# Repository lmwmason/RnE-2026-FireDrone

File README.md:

# FireDrone

FireDrone is an R&E research project on fault-aware flight-control firmware for a robotic-arm-equipped firefighting drone. It combines two distinct development tracks:

- **Mobula8 research firmware**: a real STM32F405 quadrotor running a patched Betaflight 4.4.2 build, used to validate embedded attitude estimation, bounded rate correction, logging, and safety fallbacks.
- **FireDrone X8 simulator**: a real-time X8/coaxial simulation for design studies involving wind, actuator and sensor faults, and robotic-arm reaction torque.

The project investigates how UKF attitude estimation and bounded INDI·ADRC·MRAC correction can be integrated into an existing flight stack without replacing its flight-proven rate PID, mixer, receiver, or failsafe paths.

> **Research status:** The Mobula8 firmware and associated Blackbox analysis demonstrate implementation, timing, logging, and selected flight behavior. They do **not** establish improved disturbance rejection under a controlled A/B flight experiment. The X8 airframe and robotic-arm feedforward path remain simulation/design work, not flight-validated hardware.

## Repository map

| Path | Purpose |
|---|---|
| [`firmware/mobula8/`](firmware/mobula8/) | Betaflight 4.4.2 research firmware for the real Mobula8 test vehicle, CLI snapshots, patches, host tests, firmware artifacts, and Blackbox logs. |
| [`simulation/simulator/`](simulation/simulator/) | X8 USB-joystick simulator, legacy X4/F405 SITL environment, physics model, controller core, tests, and visualizations. |
| [`PCB-Design/`](PCB-Design/) | KiCad hardware and power-system design files. |
| [`source/`](source/) | Project source material and references. |
| [`report/`](report/) | R&E report source and generated report assets. |
| [`output/`](output/) | Generated deliverables, including PDFs. |

## Control architecture

```text
RC / ANGLE reference
        │
        ▼
UKF attitude estimate ──► Betaflight outer attitude loop
                              │
                              ▼
                    Stock Betaflight rate PID
                              │
      bounded INDI · ADRC · MRAC correction (experimental)
                              │
                              ▼
                     Stock mixer / DShot motors
```

The experimental controller is intentionally **low authority**. It adds a bounded correction to the baseline PID sum only after the expected sensor, receiver, scheduler, UKF, and saturation conditions are valid. Invalid or stale estimates, timing/CPU faults, sensor faults, saturation, and mode/failsafe conditions return control to the baseline Betaflight path.

## Quick start

### X8 manual simulator

The default simulator mode is manual USB-joystick angle-mode flight.

```bash
cd simulation/simulator
./run.sh
```

Press `C` in the simulator to calibrate the joystick. See the [simulator README](simulation/simulator/README.md) for controls, fault scenarios, model assumptions, and test commands.

Useful commands:

```bash
./run.sh fpv --list-devices
./run.sh campaign --cycles 3 --laps 8
./run.sh view gust
./run.sh timing
```

### Mobula8 firmware

The Mobula8 track has hardware-specific configuration and flashing instructions. Read the [Mobula8 README](firmware/mobula8/README.md) before building, configuring, or connecting a flight battery.

```bash
cd firmware/mobula8
python3 scripts/build.py
bash scripts/test.sh
```

The generated candidate firmware is at:

```text
firmware/mobula8/dist/FireDrone_Mobula8_STM32F405_BF4.4.2_CANDIDATE.hex
```

## Evidence and validation boundaries

The project keeps simulator evidence, host tests, bench tests, Blackbox logs, and flight observations separate.

| Evidence | What it supports | What it does not support |
|---|---|---|
| Host tests | Numerical guards, bounds, reset/fallback paths, and configuration handling | Real-flight stability or performance |
| Bench Blackbox logs | Execution time, initialization, logging schema, and inactive-output checks | Closed-loop flight behavior |
| Mobula8 flight logs | Observed behavior of the real test vehicle in recorded flights | Controlled improvement claims without matched baseline trials |
| X8 simulation | Design exploration, fault-path logic, and controller integration | X8 airframe or robotic-arm flight performance |

The current Mobula8 logs and verification records are organized under [`firmware/mobula8/logs/`](firmware/mobula8/logs/). The research report and its generated PDF are in [`report/`](report/) and [`output/pdf/`](output/pdf/).

## Safety

- Remove propellers and disconnect the flight battery before firmware flashing, CLI changes, bench work, or receiver/motor checks.
- The Mobula8 firmware artifact is tied to the captured **FPVM BETAFLIGHTF4 / STM32F405** configuration. Do not flash it to another board variant based only on a similar product name.
- Preserve a full firmware readback and CLI snapshot before changing a real aircraft.
- A successful build, simulator run, host test, or flash readback does not prove safe flight.

## License

Project materials are released under the repository [LICENSE](LICENSE). Betaflight-derived components retain their respective upstream licensing terms.

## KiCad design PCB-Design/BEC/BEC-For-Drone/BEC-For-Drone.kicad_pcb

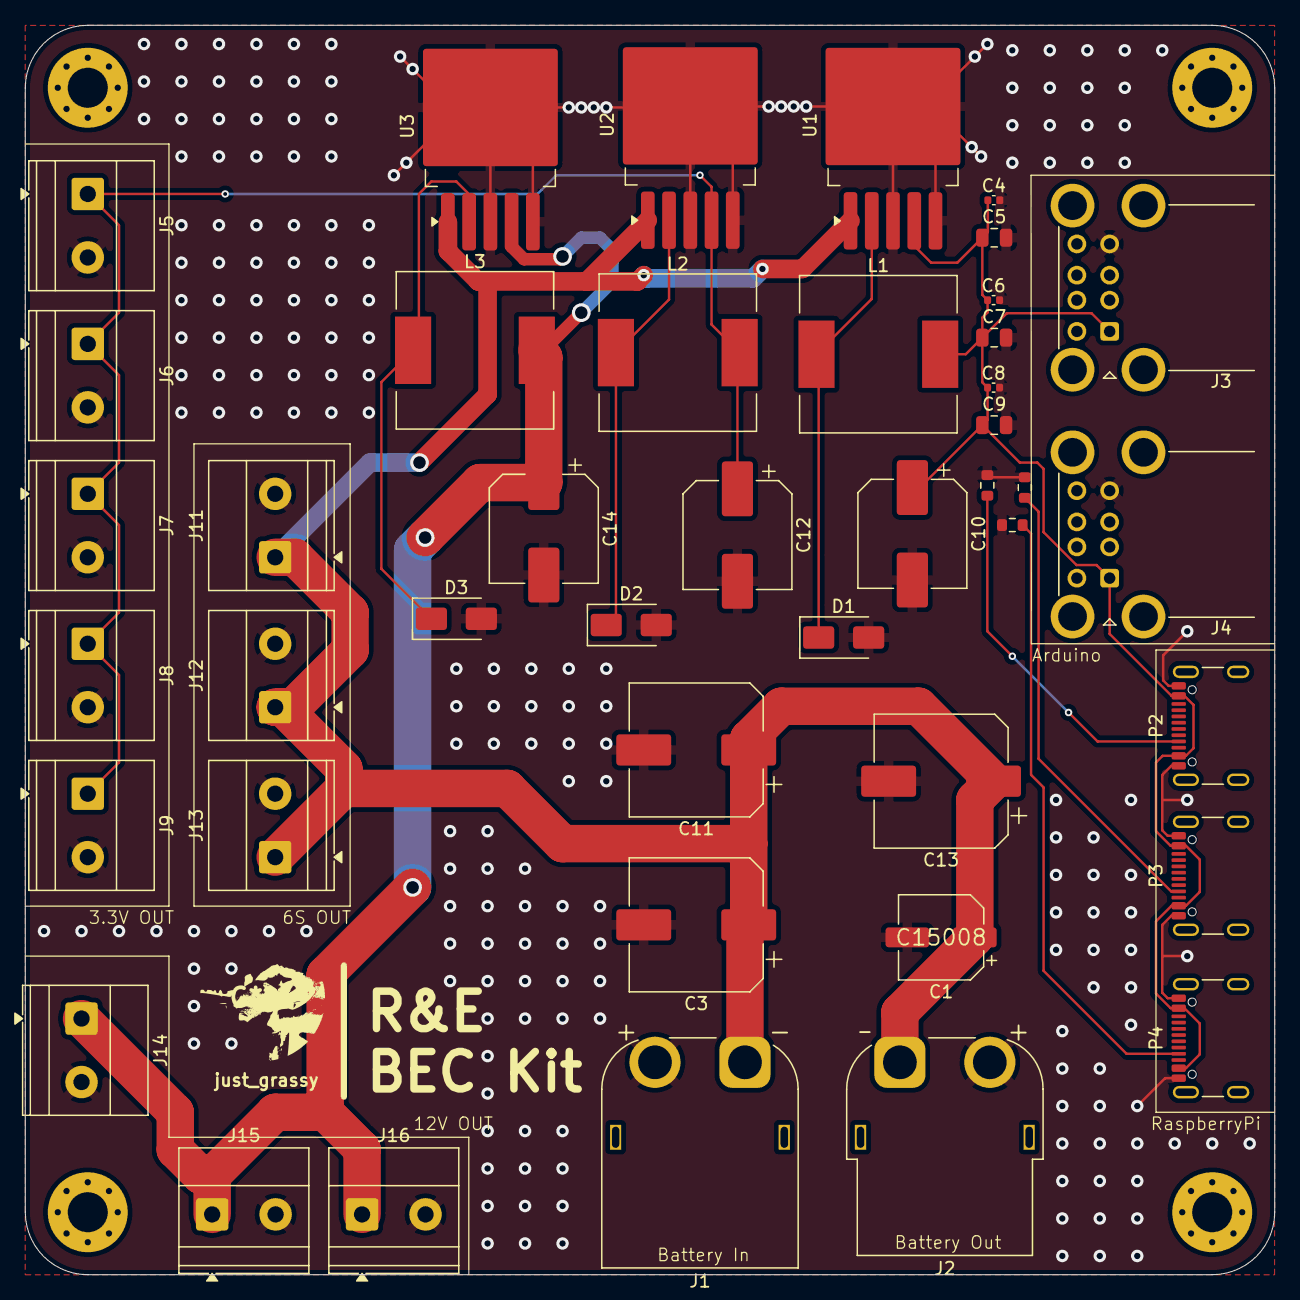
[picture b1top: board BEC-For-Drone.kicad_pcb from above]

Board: 2 copper layers, 100.0 x 100.0 mm, 47 parts (0 on the bottom side), 11 nets.

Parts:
C1: 100u; CP_Elec_6.3x7.7
C3, C11, C13: 680u; CP_Elec_10x10.5
C4, C6, C8: 100n; C_0402_1005Metric
C5, C7, C9: 10u; C_0805_2012Metric
C10, C12, C14: 220u; CP_Elec_8x10.5
D1, D2, D3: 1N5824; D_SMA
H1, H2, H3, H4: MountingHole_Pad_MP; MountingHole_3.2mm_M3_Pad_Via
J1: XT60-for-6s-battery-in; AMASS_XT60PW-M_1x02_P7.20mm_Horizontal
J2: XT60-for-6s-battery-out; AMASS_XT60PW-F_1x02_P7.20mm_Horizontal
J3, J4: USB3_A_Stacked; USB_A_CUI_UJ2-ADH-TH_Horizontal_Stacked
J5, J6, J7, J8, J9: 3.3v-Out; TerminalBlock_Phoenix_MKDS-1,5-2-5.08_1x02_P5.08mm_Horizont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
J11, J12, J13: 28v-Out; TerminalBlock_Phoenix_MKDS-1,5-2-5.08_1x02_P5.08mm_Horizont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
J14, J15, J16: 12v-Out; TerminalBlock_Phoenix_MKDS-1,5-2-5.08_1x02_P5.08mm_Horizont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
L1, L2, L3: 33u; L_12x12mm_H6mm
P2, P3, P4: USB_C_Plug_USB2.0; USB_C_Receptacle_GCT_USB4105-xx-A_16P_TopMnt_Horizontal
R2, R3, R4: 5.1K; R_0603_1608Metric
U1: LM2596S-5; TO-263-5_TabPin3
U2: LM2596S-3.3; TO-263-5_TabPin3
U3: LM2596S-12; TO-263-5_TabPin3

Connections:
+28V: C1.1, C3.1, C11.1, C13.1, J1.1, J2.1, J11.1, J12.1, J13.1, U1.1 (VIN), U2.1 (VIN), U3.1 (VIN)
/Arduino-Power/5v: C4.1, C5.1, C6.1, C7.1, C8.1, C9.1, C10.1, J3.1 (VBUS1), J4.1 (VBUS1), L1.2, P2.A4 (VBUS), P2.A9 (VBUS), P2.B4 (VBUS), P2.B9 (VBUS), P3.A4 (VBUS), P3.A9 (VBUS), P3.B4 (VBUS), P3.B9 (VBUS), P4.A4 (VBUS), P4.A9 (VBUS), P4.B4 (VBUS), P4.B9 (VBUS), U1.4 (FB)
/BatRegulate/3.3v: C12.1, J5.1, J6.1, J7.1, J8.1, J9.1, L2.2, U2.4 (FB)
/BatRegulate/12v: C14.1, J14.1, J15.1, J16.1, L3.2, U3.4 (FB)
GND: C1.2, C3.2, C4.2, C5.2, C6.2, C7.2, C8.2, C9.2, C10.2, C11.2, C12.2, C13.2, C14.2, D1.2 (A), D2.2 (A), D3.2 (A), J1.2, J2.2, J3.4 (GND1), J4.4 (GND1), J5.2, J6.2, J7.2, J8.2, J9.2, J11.2, J12.2, J13.2, J14.2, J15.2, J16.2, P2.A1 (GND), P2.A12 (GND), P2.B1 (GND), P2.B12 (GND), P3.A1 (GND), P3.A12 (GND), P3.B1 (GND), P3.B12 (GND), P4.A1 (GND), P4.A12 (GND), P4.B1 (GND), P4.B12 (GND), R2.2, R3.2, R4.2, U1.3 (GND), U1.5 (~ON/OFF), U2.3 (GND), U2.5 (~ON/OFF), U3.3 (GND), U3.5 (~ON/OFF)
unnamed: D1.1 (K), L1.1, U1.2 (OUT)
unnamed: D2.1 (K), L2.1, U2.2 (OUT)
unnamed: D3.1 (K), L3.1, U3.2 (OUT)
unnamed: P2.A5 (CC), R2.1
unnamed: P3.A5 (CC), R3.1
unnamed: P4.A5 (CC), R4.1

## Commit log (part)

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2026-03-10 Test lidar and visualize lidar!
2026-04-19 END BEC-PCB design
2026-05-29 jiojiojoii
